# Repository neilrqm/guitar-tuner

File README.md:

guitar-tuner
============

Design files and source code for a stroboscopic guitar tuner.

The design files are in the pcb/ directory.  To view the project, 
open the tuner.pro file in KiCAD (http://www.kicad-pcb.org/).

The source code is in the src/ directory.  It's pretty buggy.

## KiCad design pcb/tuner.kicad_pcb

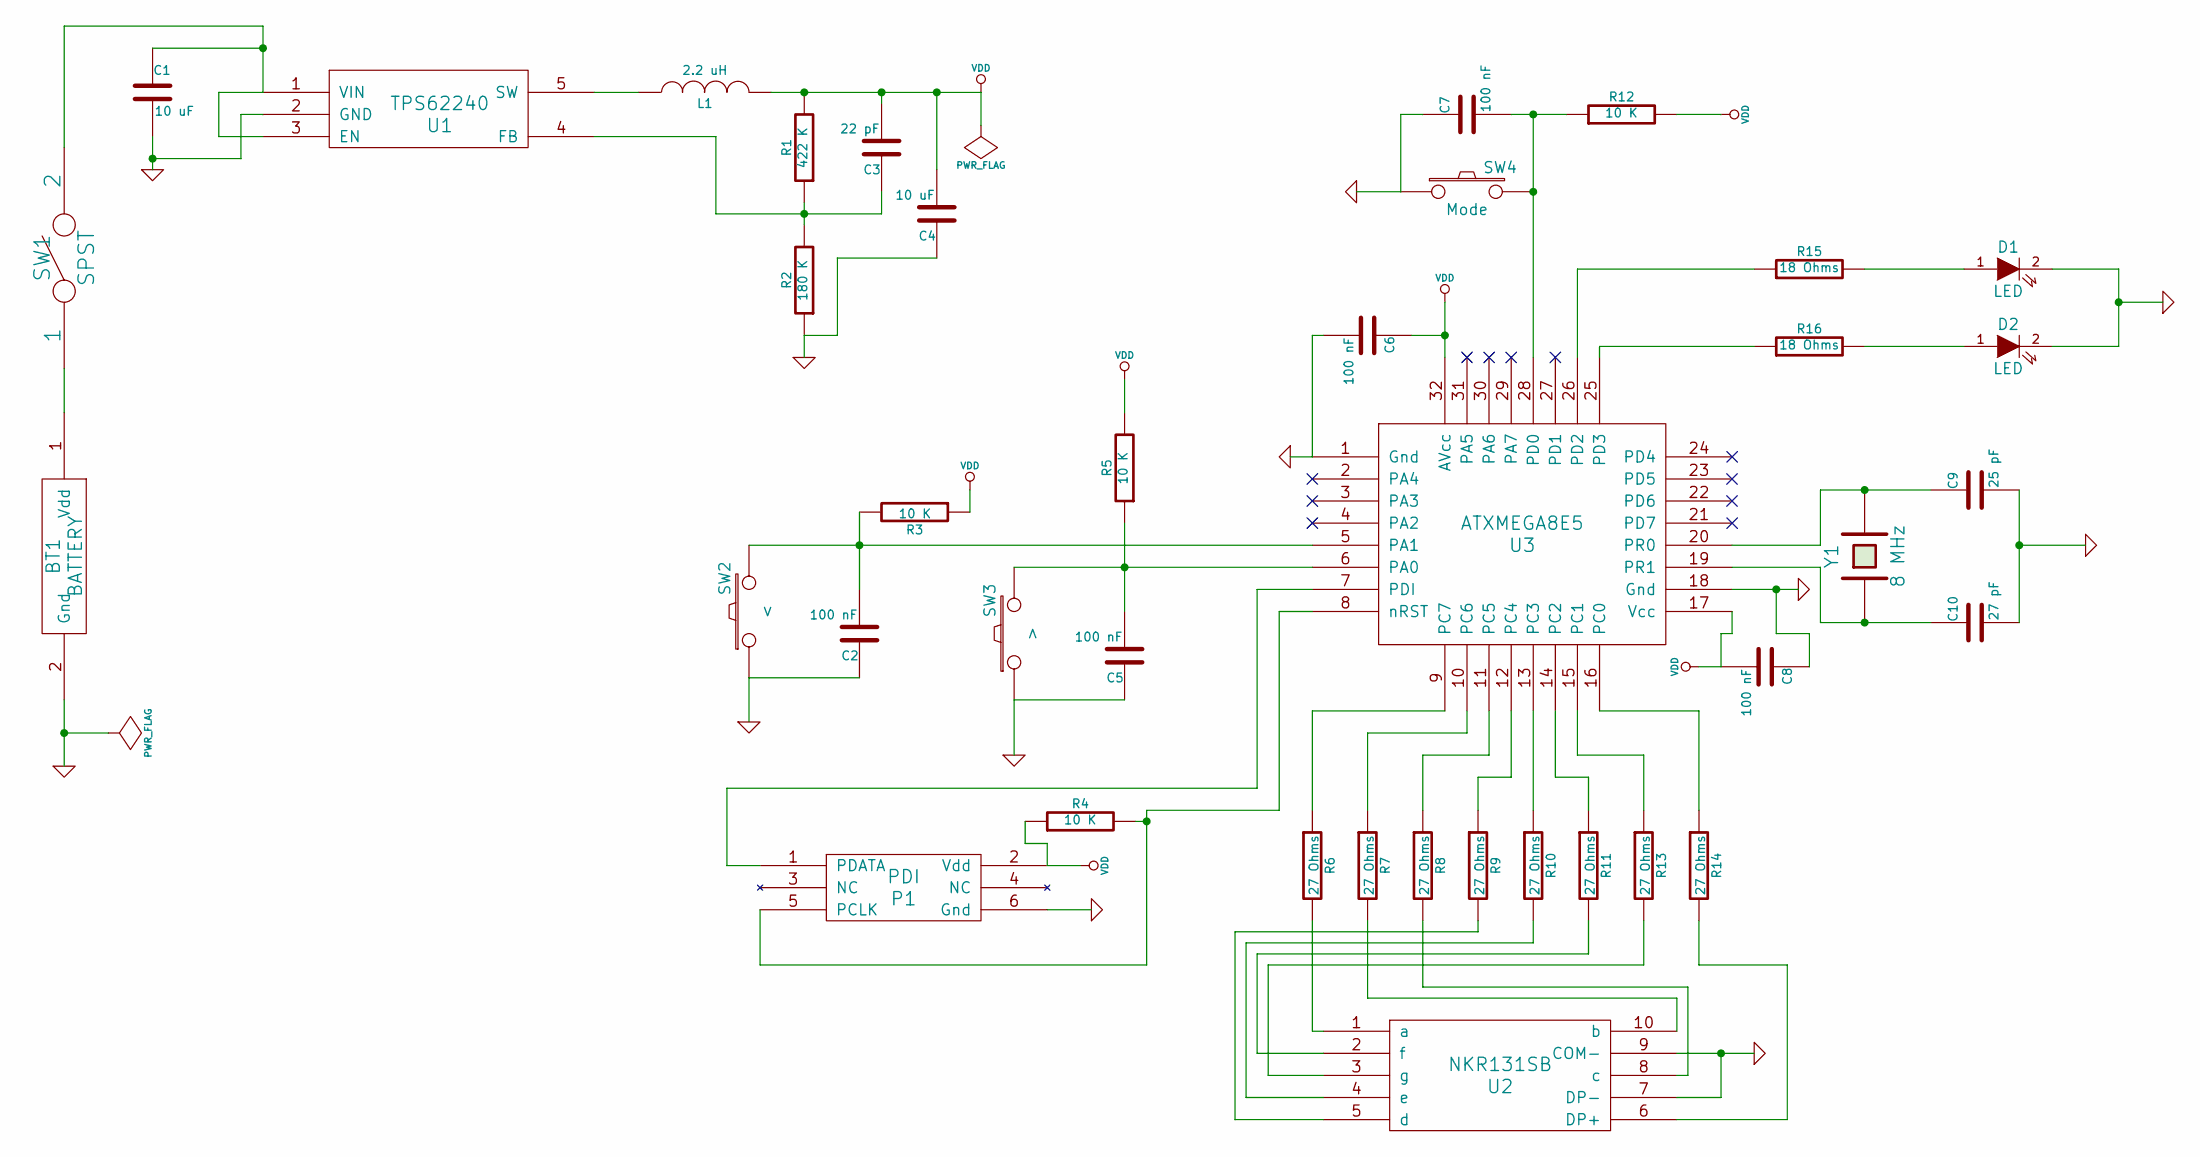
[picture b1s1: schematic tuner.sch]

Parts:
BT1: BATTERY
C1, C4: 10 uF
C2, C5, C6, C7, C8: 100 nF
C3: 22 pF
C9: 25 pF
C10: 27 pF
D1, D2: LED
L1: 2.2 uH
P1: PDI
R1: 422 K
R2: 180 K
R3, R4, R5, R12: 10 K
R6, R7, R8, R9, R10, R11, R13, R14: 27 Ohms
R15, R16: 18 Ohms
SW1: SPST
SW2: <
SW3: >
SW4: Mode
U1: TPS62240
U2: NKR131SB
U3: ATXMEGA8E5
Y1: 8 MHz

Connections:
GND: BT1.2 (Gnd), C1.2, C2.1, C4.1, C5.1, C6.2, C7.1, C8.1, C9.2, C10.2, D1.2 (K), D2.2 (K), P1.6 (Gnd), R2.1, SW2.1, SW3.1, SW4.1, U1.2 (GND), U2.7 (DP-), U2.9 (COM-), U3.1 (Gnd), U3.18 (Gnd)
unnamed: R7.1, U3.10 (PC6)
unnamed: R11.1, U3.14 (PC2)
unnamed: R10.1, U3.13 (PC3)
unnamed: R9.1, U3.12 (PC4)
unnamed: R8.1, U3.11 (PC5)
unnamed: R6.1, U3.9 (PC7)
unnamed: R14.2, U2.6 (DP+)
unnamed: R13.2, U2.3 (g)
unnamed: D2.1 (A), R16.2
unnamed: R16.1, U3.25 (PD3)
unnamed: R15.1, U3.26 (PD2)
unnamed: D1.1 (A), R15.2
unnamed: R14.1, U3.16 (PC0)
unnamed: R13.1, U3.15 (PC1)
unnamed: R6.2, U2.1 (a)
unnamed: R9.2, U2.5 (d)
unnamed: R11.2, U2.2 (f)
unnamed: R10.2, U2.4 (e)
unnamed: R8.2, U2.8 (c)
unnamed: R7.2, U2.10 (b)
unnamed: C2.2, R3.2, SW2.2, U3.5 (PA1)
unnamed: C5.2, R5.1, SW3.2, U3.6 (PA0)
unnamed: P1.5 (PCLK), R4.2, U3.8 (nRST)
unnamed: P1.1 (PDATA), U3.7 (PDI)
unnamed: C3.1, R1.1, R2.2, U1.4 (FB)
unnamed: L1.1, U1.5 (SW)
unnamed: C1.1, SW1.2, U1.1 (VIN), U1.3 (EN)
unnamed: BT1.1 (Vdd), SW1.1
unnamed: C9.1, U3.20 (PR0), Y1.2
unnamed: C7.2, R12.1, SW4.2, U3.28 (PD0)
unnamed: C10.1, U3.19 (PR1), Y1.1
VDD: C3.2, C4.2, C6.1, C8.2, L1.2, P1.2 (Vdd), R1.2, R3.1, R4.1, R5.2, R12.2, U3.17 (Vcc), U3.32 (AVcc)

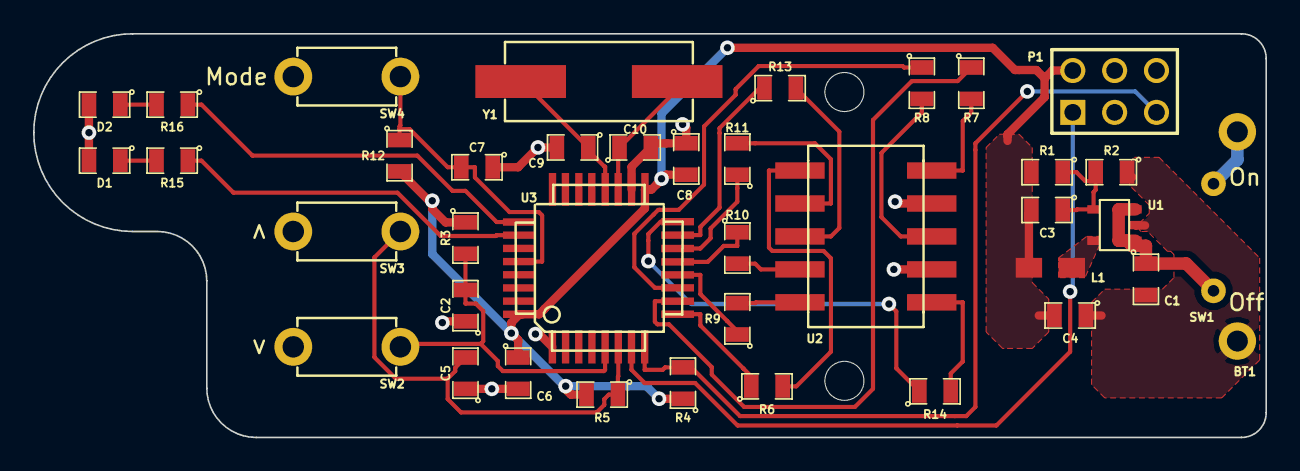
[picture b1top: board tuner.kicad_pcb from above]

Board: 2 copper layers, 74.8 x 24.5 mm, 39 parts (1 on the bottom side), 33 nets.

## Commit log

2014-01-29 Added hardware source files
2014-01-30 Mostly finished layout.
2014-01-30 Added gerber files.
2014-01-30 No change...
2014-01-31 - Generated traces - Changed battery holder mounting holes to non-plated through holes and modified the drill file accordingly. - Re-generated output files.
2014-02-01 Rearranged layout to be more compact, reduced board length.
2014-02-08 Swapped the LEDs to avoid crossing wires, tweaked some stuff, added a ground plane.
2014-02-09 Final tweaks to PCB layout, added CC BY-SA license. This commit corresponds to the initial PCB run.
2014-02-28 - Added manufacturer, part number, and description fields to BOM - Changed MCU info to an equivalent that is available
2014-02-28 Removed library cache.
2014-03-05 Added bare Atmel Studio project for guitar tuner code.
2014-03-07 Added config code and LED defines.
2014-03-07 Rethought naming scheme.
2014-03-16 Moved some stuff around, finished code structure, ready to test.
2014-03-19 A bunch of code fixes to make it kind of work.
2016-10-09 - Converted hardware design files to KiCAD 4.x format - Created footprints for new parts in r3 hardware design - Revised schematic and footprint associations for r3 hardware design

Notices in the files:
pcb/tuner.kicad_pcb:
CC BY-SA License: http://creativecommons.org/licenses/by-sa/4.0/legalcode
CC BY-SA 4.0
